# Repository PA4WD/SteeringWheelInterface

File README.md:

Steering wheel interface for Nissan Note 2006  to Kenwood NEC remote input

orginal wiring  in the car

Resistor values from the steering wheel buttons

Connect info button \n radio connector to ground.

NEC Radio codes for the Kenwood

| meaning    | code   |
|------------|--------|
| tuner      | 0xb91c |
| tape       | 0xb91d |
| cd         | 0xb91e |
| cd-md-ch   | 0xb91f |
| track-     | 0xb90a |
| track+     | 0xb90b |
| rew        | 0xb90c |
| ff         | 0xb90d |
| dnpp (?)   | 0xb95e |
| play/pause | 0xb90e |
| ---        |        |
| volume+    | 0xb914 |
| volume-    | 0xb915 |
| source     | 0xb913 |
| mute       | 0xb916 |
| ---        |        |
| 0          | 0xb900 |
| 1          | 0xb901 |
| 2          | 0xb902 |
| 3          | 0xb903 |
| 4          | 0xb904 |
| 5          | 0xb905 |
| 6          | 0xb906 |
| 7          | 0xb907 |
| 8          | 0xb908 |
| 9          | 0xb909 |

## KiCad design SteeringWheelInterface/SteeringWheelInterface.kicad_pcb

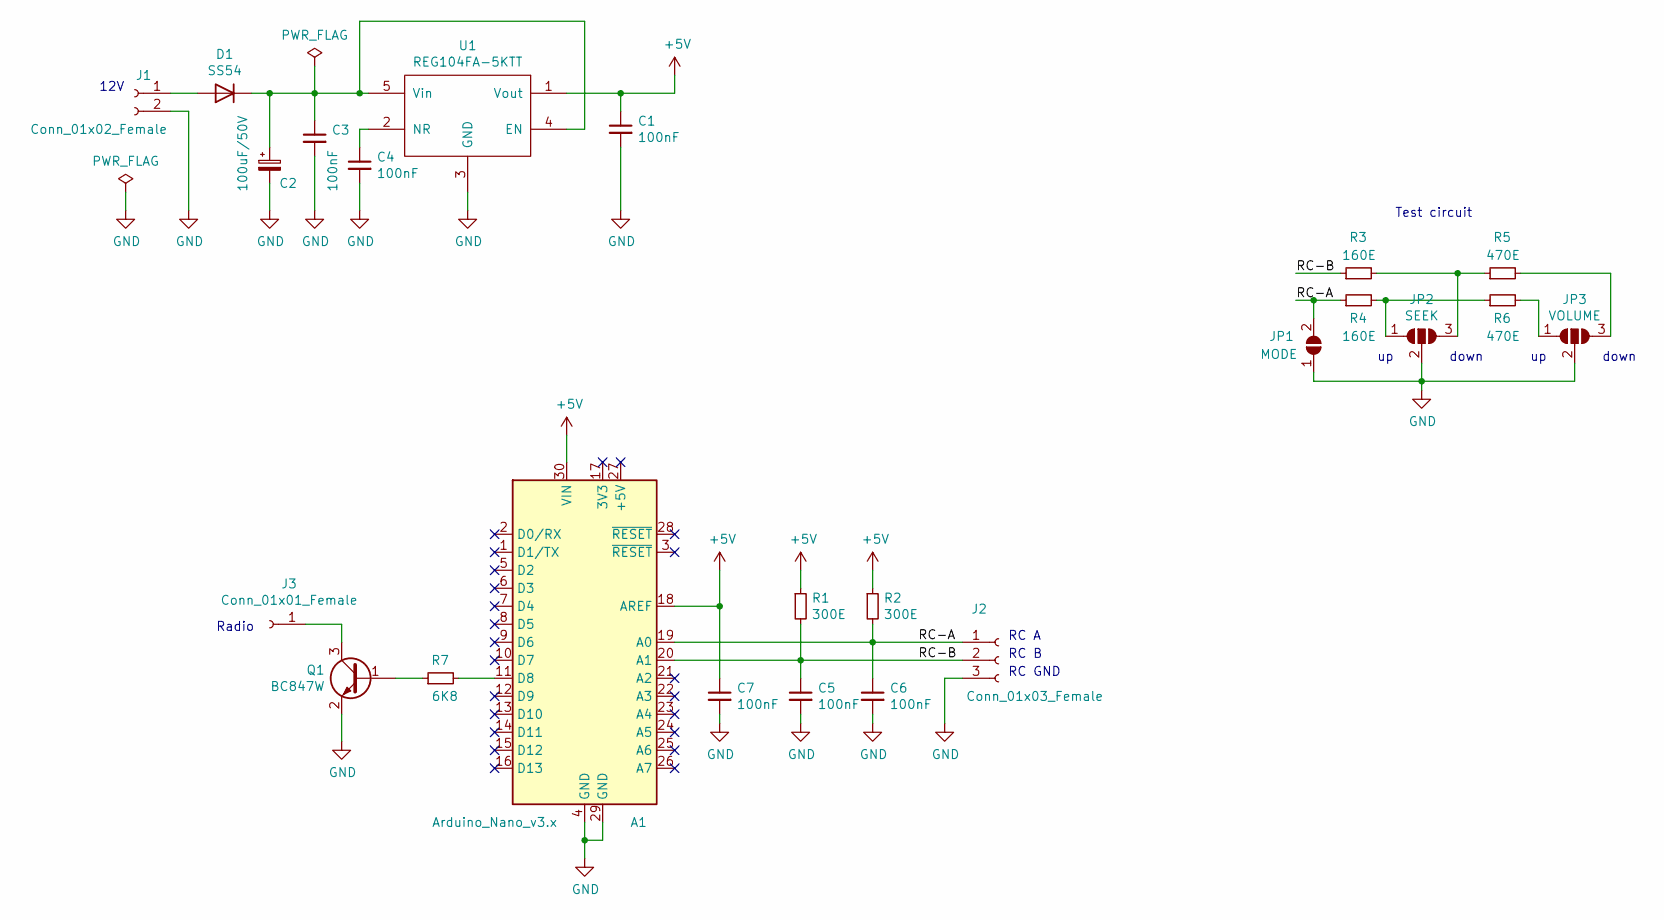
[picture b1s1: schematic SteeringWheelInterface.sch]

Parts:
A1: Arduino_Nano_v3.x; Arduino_Nano
C1, C3, C4, C5, C6, C7: 100nF; C_1206_3216Metric_Pad1.42x1.75mm_HandSolder
C2: 100uF/50V; CP_Radial_D8.0mm_P3.80mm
D1: SS54; D_2114_3652Metric_Pad1.85x3.75mm_HandSolder
J1: Conn_01x02_Female; PinHeader_1x02_P2.54mm_Vertical
J2: Conn_01x03_Female; PinHeader_1x03_P2.54mm_Vertical
J3: Conn_01x01_Female; PinHeader_1x01_P2.54mm_Vertical
JP1: MODE; SolderJumper-2_P1.3mm_Open_Pad1.0x1.5mm
JP2: SEEK; SolderJumper-3_P1.3mm_Open_Pad1.0x1.5mm
JP3: VOLUME; SolderJumper-3_P1.3mm_Open_Pad1.0x1.5mm
Q1: BC847W; SOT-323_SC-70
R1, R2: 300E; R_1206_3216Metric_Pad1.42x1.75mm_HandSolder
R3, R4: 160E; R_1206_3216Metric_Pad1.42x1.75mm_HandSolder
R5, R6: 470E; R_1206_3216Metric_Pad1.42x1.75mm_HandSolder
R7: 6K8; R_1206_3216Metric_Pad1.42x1.75mm_HandSolder
U1: REG104FA-5KTT; TO-263-5_TabPin3

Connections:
+5V: A1.18 (AREF), A1.30 (VIN), C1.1, C7.1, R1.1, R2.1, U1.1 (Vout)
/RC-A: A1.19 (A0), C6.1, J2.1, JP1.2 (B), R2.2, R4.1
/RC-B: A1.20 (A1), C5.1, J2.2, R1.2, R3.1
GND: A1.4 (GND), A1.29 (GND), C1.2, C2.2, C3.2, C4.2, C5.2, C6.2, C7.2, J1.2, J2.3, JP1.1 (A), JP2.2 (C), JP3.2 (C), Q1.2 (E), U1.3 (GND)
unnamed: A1.11 (D8), R7.2
unnamed: C2.1, C3.1, D1.1 (K), U1.4 (EN), U1.5 (Vin)
unnamed: C4.1, U1.2 (NR)
unnamed: D1.2 (A), J1.1
unnamed: J3.1, Q1.3 (C)
unnamed: JP2.1 (A), R4.2, R6.1
unnamed: JP2.3 (B), R3.2, R5.1
unnamed: JP3.1 (A), R6.2
unnamed: JP3.3 (B), R5.2
unnamed: Q1.1 (B), R7.1

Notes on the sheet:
12V
RC A
RC B
RC GND
Radio
down
Test circuit

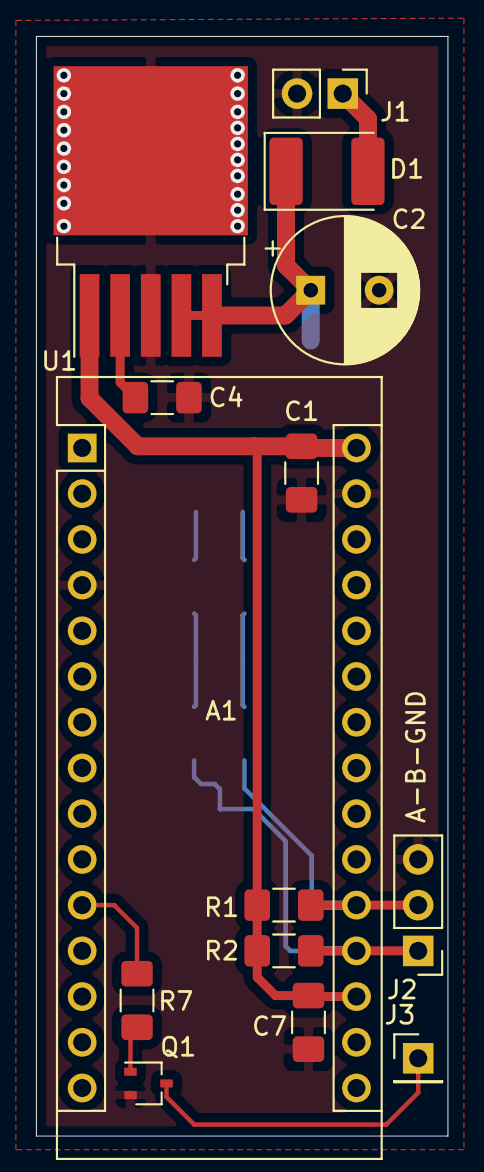
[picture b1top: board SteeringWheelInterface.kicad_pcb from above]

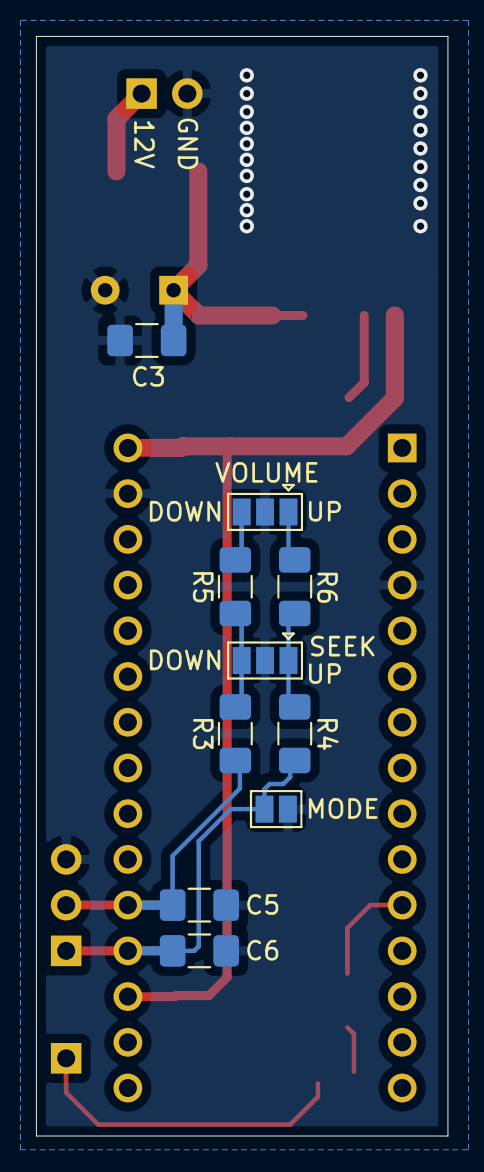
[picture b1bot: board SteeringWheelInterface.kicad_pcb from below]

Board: 2 copper layers, 22.9 x 61.1 mm, 24 parts (10 on the bottom side), 14 nets.

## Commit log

2021-02-27 Update README.md
    Show schematic in readme
2021-02-27 Update README.md
    Show images
